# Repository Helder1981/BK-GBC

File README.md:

# BK-GBC
Burger King Gameboy Color Toy PCBs for use with a Raspberry Pi Zero W and a SPI 2.0inch LCD linked below:<br>
https://www.aliexpress.com/item/QVGA320240-2-inch-SPI-serial-screen-320-240-12pin-ST7789V-2-0-inch-LCD/32906389474.html

If you use these or edit them please leave my name or mention of where you got them.

Installation of Drivers (Run each command one line at a time in the terminal unless specified):

`sudo nano /etc/modules-load.d/fbtft.conf`<br>
add these 2 lines to the file<br>
`spi-bcm2835`<br>
`fbtft_device`<br>
Ctrl + O to save then Ctrl + X to exit

-------------------------------------------------

`sudo nano /etc/modprobe.d/fbtft.conf`<br>

copy entire code below into the opened file<br>

`options fbtft_device custom name=fb_st7789v speed=81000000 rotate=270 fps=60 buswidth=8  gpios=reset:25,dc:24 modprobe flexfb setaddrwin=0 width=240 height=320 init=-1,0x11,-2,120,-1,0x36,0x00,-1,0x3A,0x05,-1,0xB2,0x08,0x08,0x00,0x33,0x33,-1,0xB7,0x35,-1,0xBB,0x1A,-1,0xC2,0x01,-1,0xC3,0x3F,-1,0xC4,0x26,-1,0xC6,0x0E,-1,0xD0,0xA4,0xA1,-1,0x21,-1,0xE0,0x00,0x19,0x1E,0x0A,0x09,0x15,0x3D,0x44,0x51,0x12,0x03,0x00,0x3F,0x3F,-1,0xE1,0x00,0x18,0x1E,0x0A,0x09,0x25,0x3F,0x43,0x52,0x33,0x03,0x00,0x3F,0x3F,-1,0x29,-3`<br>
<br>
Ctrl + O to save then Ctrl + X to exit

-------------------------------------------------

Now it's time to install the FBCP software (enter 1 line at a time)

`sudo apt-get update`<br>
`sudo apt-get install cmake git`<br>
`git clone https://github.com/tasanakorn/rpi-fbcp`<br>
`cd rpi-fbcp/`<br>
`mkdir build`<br>
`cd build/`<br>
`cmake ..`<br>
`make`<br>
`sudo install fbcp /usr/local/bin/fbcp`<br>
<br>
Ctrl + O to save then Ctrl + X to exit

----------------------------------------------------

We need to add the fbcp to boot everytime to initiate the LCD so we are going to edit a file and add a line of code for this 

`sudo echo "/usr/local/bin/fbcp &" >> /etc/rc.local`

----------------------------------------------------

We need to edit the config.txt and add these lines at the end of the text file.

`sudo nano /boot/config.txt`<br><br>
`hdmi_force_hotplug=1`<br>
`hdmi_group=2`<br>
`hdmi_mode=87`<br>
`hdmi_cvt=640 480 60 1 0 0 0`<br>
`disable_overscan=1`<br>
`dtparam=spi=on`<br>
<br>
Ctrl + O to save then Ctrl + X to exit

Finally Reboot the Pi and see the LCD work by typing:
`sudo reboot -h now`

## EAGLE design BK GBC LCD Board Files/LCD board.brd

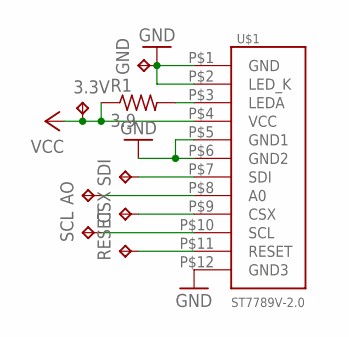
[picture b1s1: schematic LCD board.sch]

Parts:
3.3V: TPTP18RECT; TP18RECT
AO: TPTP18RECT; TP18RECT
CSX: TPTP18RECT; TP18RECT
GND: TPTP18RECT; TP18RECT
R1: 3.9; R0603
RESET: TPTP18RECT; TP18RECT
SCL: TPTP18RECT; TP18RECT
SDI: TPTP18RECT; TP18RECT
U$1: ST7789V-2.0

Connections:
GND: GND.TP, U$1.P$1 (GND), U$1.P$2 (LED_K), U$1.P$5 (GND1), U$1.P$6 (GND2), U$1.P$12 (GND3)
unnamed: R1.2, U$1.P$3 (LEDA)
unnamed: SDI.TP, U$1.P$7 (SDI)
unnamed: AO.TP, U$1.P$8 (A0)
unnamed: CSX.TP, U$1.P$9 (CSX)
unnamed: SCL.TP, U$1.P$10 (SCL)
unnamed: RESET.TP, U$1.P$11 (RESET)
VCC: 3.3V.TP, R1.1, U$1.P$4 (VCC)

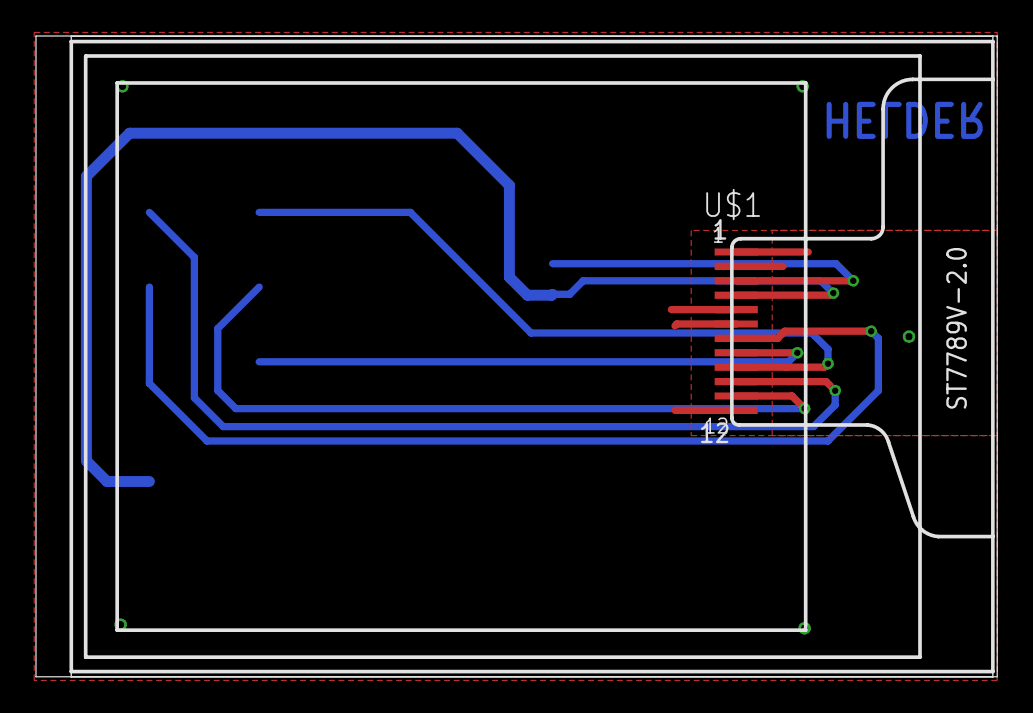
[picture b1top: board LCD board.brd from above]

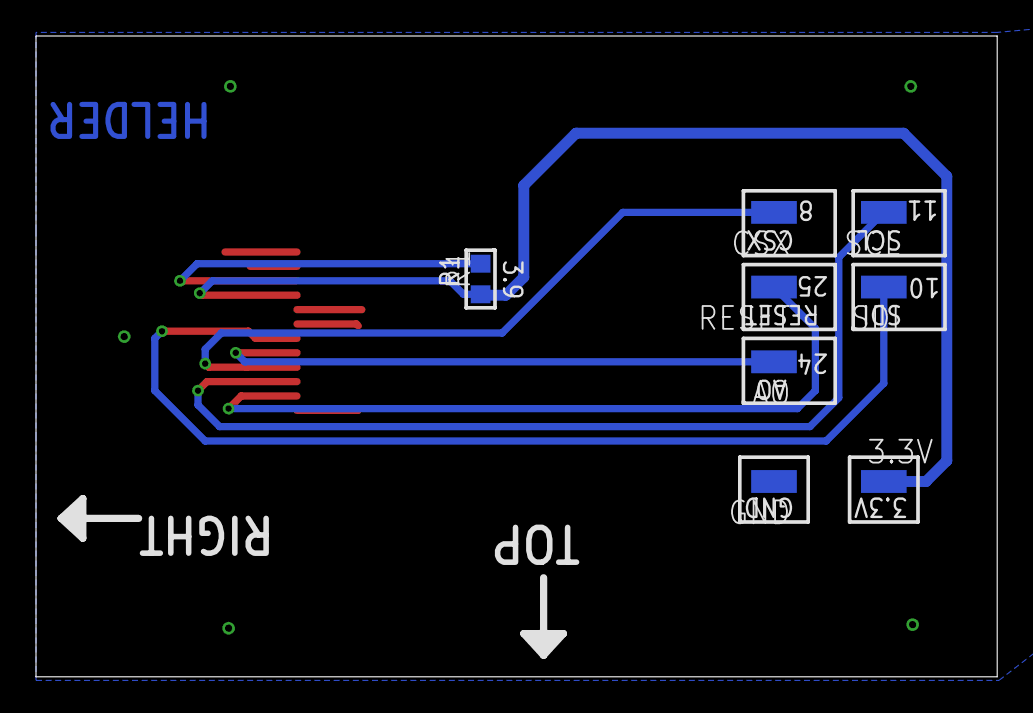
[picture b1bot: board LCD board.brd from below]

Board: 2 copper layers, 53.4 x 35.6 mm, 9 parts (8 on the bottom side), 8 nets.

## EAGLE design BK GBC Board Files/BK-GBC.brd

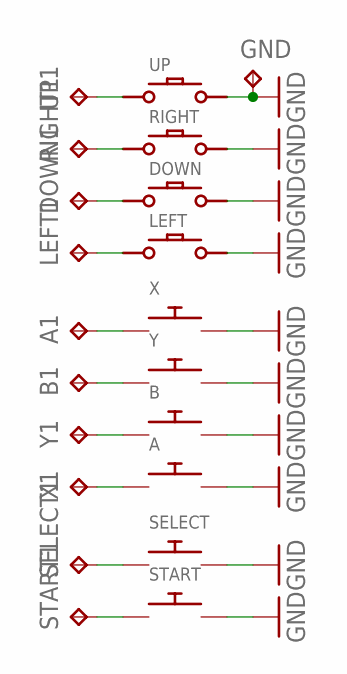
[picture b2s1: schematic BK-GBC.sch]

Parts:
A: SWITCH_PUSH_VMUHOLE; KEYPAD-VMU-HOLE
A1: TPPAD1-17; P1-17
B: SWITCH_PUSH_VMUHOLE; KEYPAD-VMU-HOLE
B1: TPPAD1-17; P1-17
DOWN: DMG-BTNDPAD; DS-LITE-DPAD
DOWN1: TPPAD1-17; P1-17
GND: TPPAD1-17; P1-17
LEFT: DMG-BTNDPAD; DS-LITE-DPAD
LEFT1: TPPAD1-17; P1-17
RIGHT: DMG-BTNDPAD; DS-LITE-DPAD
RIGHT1: TPPAD1-17; P1-17
SELECT: SWITCH_PUSH_VMUSMALL-PAD; SMALL_KEYPAD
SELECT1: TPPAD1-17; P1-17
START: SWITCH_PUSH_VMUSMALL-PAD; SMALL_KEYPAD
START1: TPPAD1-17; P1-17
UP: DMG-BTNDPAD; DS-LITE-DPAD
UP1: TPPAD1-17; P1-17
X: SWITCH_PUSH_VMULARGE-PAD; KEYPAD_VMU_R26
X1: TPPAD1-17; P1-17
Y: SWITCH_PUSH_VMULARGE-PAD; KEYPAD_VMU_R26
Y1: TPPAD1-17; P1-17

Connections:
GND: A.2, B.2, DOWN.P$4, GND.TP, LEFT.P$4, RIGHT.P$4, SELECT.2, START.2, UP.P$4, X.2, Y.2
unnamed: UP.P$3, UP1.TP
unnamed: RIGHT.P$3, RIGHT1.TP
unnamed: DOWN.P$3, DOWN1.TP
unnamed: LEFT.P$3, LEFT1.TP
unnamed: A1.TP, X.1
unnamed: B1.TP, Y.1
unnamed: B.1, Y1.TP
unnamed: A.1, X1.TP
unnamed: SELECT.1, SELECT1.TP
unnamed: START.1, START1.TP

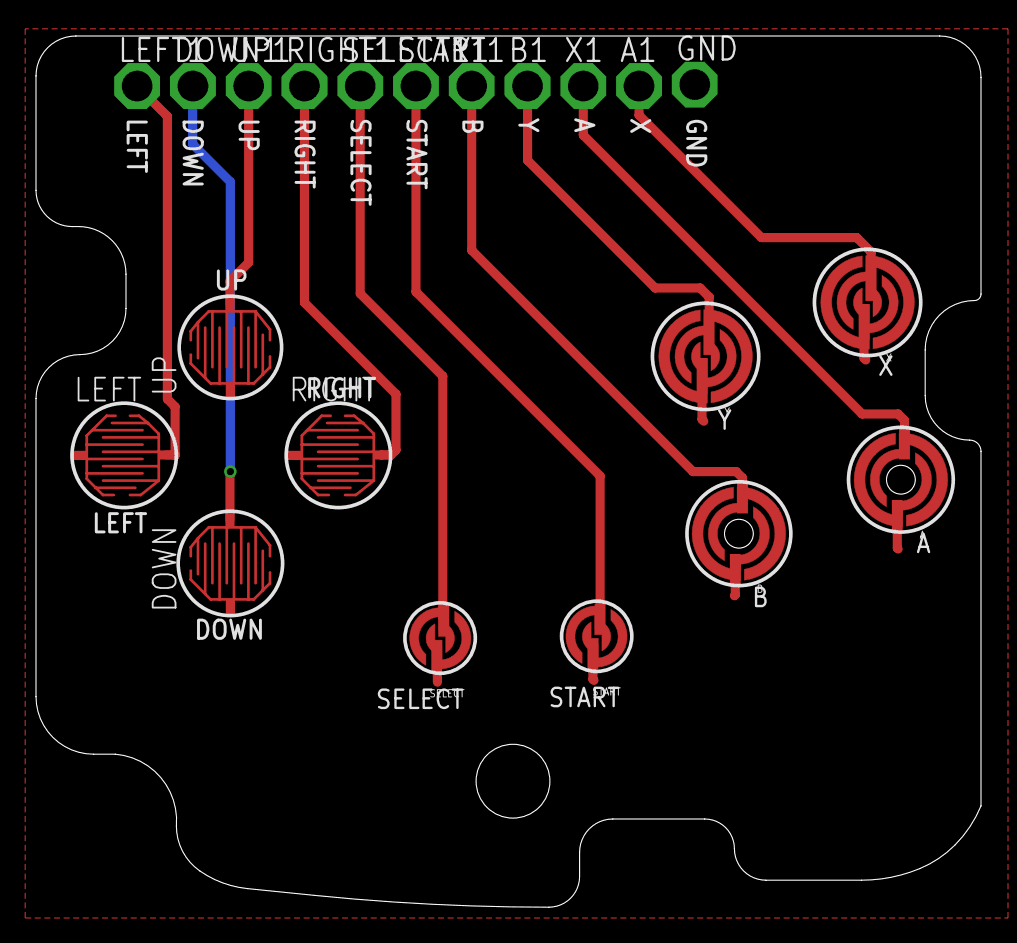
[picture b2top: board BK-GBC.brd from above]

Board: 2 copper layers, 52.5 x 48.4 mm, 21 parts (0 on the bottom side), 11 nets.
